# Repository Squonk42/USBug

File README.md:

USBug Development Board
=====

The USBug is a complete USB-based microcontroller development system in a very small footprint.
All programming is done via the USB port. No special programmer is needed, only a standard "Mini-B" USB cable and a Windows/Linux PC or a Macintosh with a USB port are required.

Key features:
 - Fully Open-Source Hardware & Software (CC-BY-SA, GPL)
 - Drag & Drop firmware, just use it as an USB Memory Stick!
 - No Loader application, the bootloader resides in ROM (unereasable)
 - Works with Mac OS X, Linux & Windows
 - Standard ARM SWD debug/trace connector
 - ARM "Cortex M3" 32-bit processor, up to 72 MHz, up to 64 kB Flash, up to 10 kB SRAM
 - Up to 42 GPIO pins, 1xUSB device, 1xUART, 1xI2C, 1xSPI interfaces
 - 2x32-bit, 2x16-bit, 1xWatchdog timers
 - 10 Bit ADC with up to 8 inputs
 - Tiny size: 2" x 0.8" (50 mm x 20 mm), only 0.244" (6.2 mm) thick (w/o header pins)
 - Available with pins for solderless breadboard
 - Very low cost & low shipping options

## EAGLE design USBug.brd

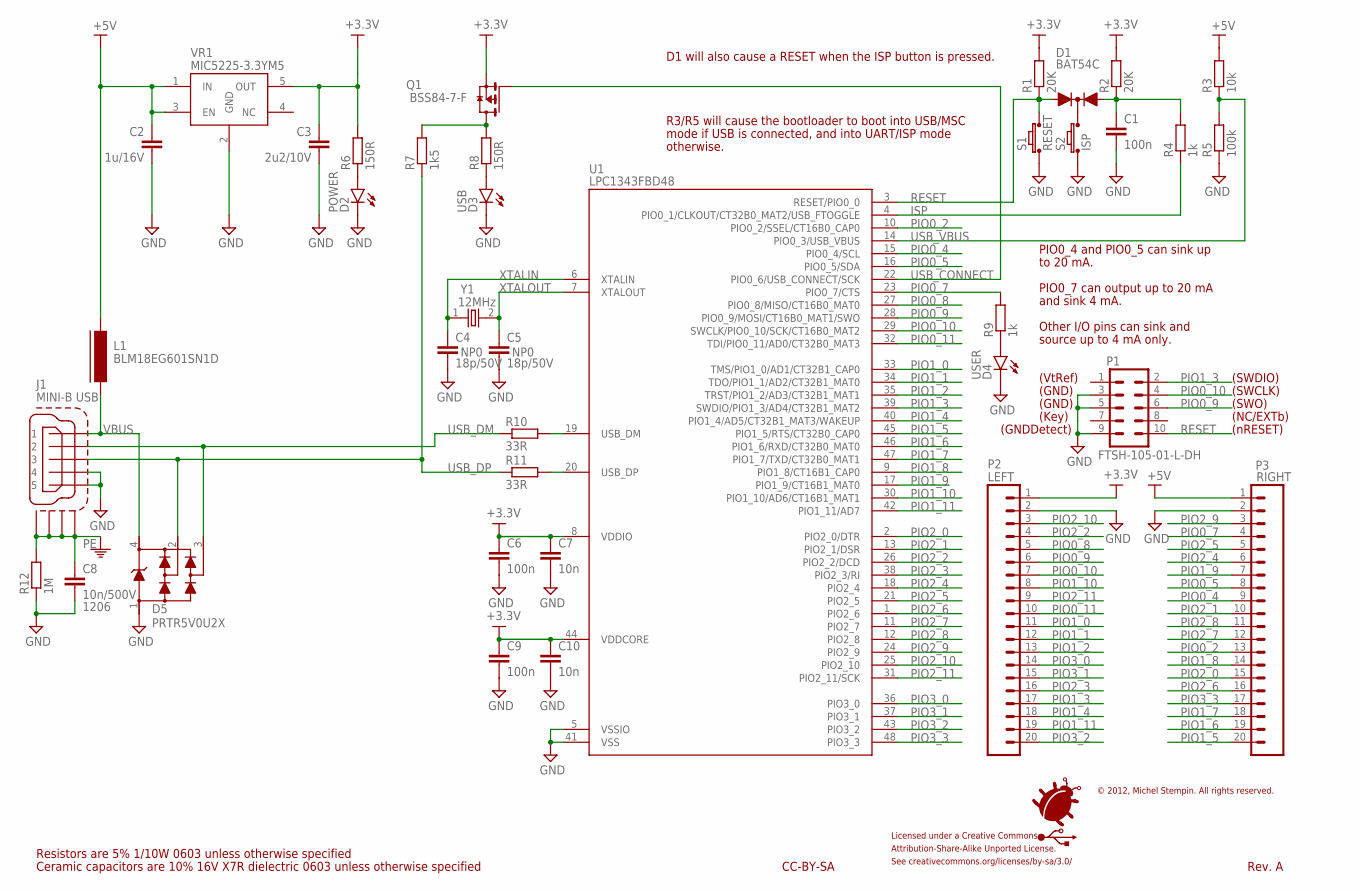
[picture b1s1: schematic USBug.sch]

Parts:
C1, C6, C9: 100n; CAP_0603
C2: 1u/16V; CAP_0603
C3: 2u2/10V; CAP_0603
C4, C5: 18p/50V; CAP_0603
C7, C10: 10n; CAP_0603
C8: 10n/500V; CAP_1206
D1: BAT54C; SOT23-R
D2: POWER; LED_0805
D3: USB; LED_0805
D4: USER; LED_0805
D5: PRTR5V0U2X; SOT143B
J1: MINI-B USB; UX60-MB-5ST
L1: BLM18EG601SN1D; FB_0603
LOGO: USBUG
P1: FTSH-105-01-L-DH
P2: LEFT; SPARKFUN_1X20_LOCK
P3: RIGHT; SPARKFUN_1X20_LOCK
Q1: BSS84-7-F; SOT23-R
R1, R2: 20K; RES_0603
R3: 10k; RES_0603
R4, R9: 1k; RES_0603
R5: 100k; RES_0603
R6, R8: 150R; RES_0603
R7: 1k5; RES_0603
R10, R11: 33R; RES_0603
R12: 1M; RES_0603
S1: RESET; ADTSM3
S2: ISP; ADTSM3
U1: LPC1343FBD48; LQFP48
VR1: MIC5225-3.3YM5; SOT23-5
Y1: 12MHz; NX5032GA

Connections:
+3.3V: C3.1, C6.1, C7.1, C9.1, C10.1, P2.1, Q1.2 (S), R1.2, R2.2, R6.2, U1.8 (VDDIO), U1.44 (VDDCORE), VR1.5 (OUT)
+5V: C2.1, L1.1, P3.1, R3.2, VR1.1 (IN), VR1.3 (EN)
GND: C1.2, C2.2, C3.2, C4.2, C5.2, C6.2, C7.2, C8.2, C9.2, C10.2, D2.C, D3.C, D4.C, D5.1, J1.4, J1.5, P1.3, P1.5, P1.9, P2.2, P3.2, R5.1, R12.1, S1.2, S2.2, U1.5 (VSSIO), U1.41 (VSS), VR1.2 (GND)
ISP: R4.1, U1.4 (PIO0_1/CLKOUT/CT32B0_MAT2/USB_FTOGGLE)
unnamed: D1.3 (C), S2.1
unnamed: C1.1, D1.2 (A2), R2.1, R4.2
unnamed: D2.A, R6.1
unnamed: D4.A, R9.1
unnamed: D3.A, R8.1
unnamed: Q1.3 (D), R7.2, R8.2
PE: C8.1, J1.M1, J1.M2, J1.M3, J1.M4, R12.2
PIO0_2: P3.13, U1.10 (PIO0_2/SSEL/CT16B0_CAP0)
PIO0_4: P3.9, U1.15 (PIO0_4/SCL)
PIO0_5: P3.8, U1.16 (PIO0_5/SDA)
PIO0_7: P3.4, R9.2, U1.23 (PIO0_7/CTS)
PIO0_8: P2.5, U1.27 (PIO0_8/MISO/CT16B0_MAT0)
PIO0_9: P1.6, P2.6, U1.28 (PIO0_9/MOSI/CT16B0_MAT1/SWO)
PIO0_10: P1.4, P2.7, U1.29 (SWCLK/PIO0_10/SCK/CT16B0_MAT2)
PIO0_11: P2.10, U1.32 (TDI/PIO0_11/AD0/CT32B0_MAT3)
PIO1_0: P2.11, U1.33 (TMS/PIO1_0/AD1/CT32B1_CAP0)
PIO1_1: P2.12, U1.34 (TDO/PIO1_1/AD2/CT32B1_MAT0)
PIO1_2: P2.13, U1.35 (TRST/PIO1_2/AD3/CT32B1_MAT1)
PIO1_3: P1.2, P2.17, U1.39 (SWDIO/PIO1_3/AD4/CT32B1_MAT2)
PIO1_4: P2.18, U1.40 (PIO1_4/AD5/CT32B1_MAT3/WAKEUP)
PIO1_5: P3.20, U1.45 (PIO1_5/RTS/CT32B0_CAP0)
PIO1_6: P3.19, U1.46 (PIO1_6/RXD/CT32B0_MAT0)
PIO1_7: P3.18, U1.47 (PIO1_7/TXD/CT32B0_MAT1)
PIO1_8: P3.14, U1.9 (PIO1_8/CT16B1_CAP0)
PIO1_9: P3.7, U1.17 (PIO1_9/CT16B1_MAT0)
PIO1_10: P2.8, U1.30 (PIO1_10/AD6/CT16B1_MAT1)
PIO1_11: P2.19, U1.42 (PIO1_11/AD7)
PIO2_0: P3.15, U1.2 (PIO2_0/DTR)
PIO2_1: P3.10, U1.13 (PIO2_1/DSR)
PIO2_2: P2.4, U1.26 (PIO2_2/DCD)
PIO2_3: P2.16, U1.38 (PIO2_3/RI)
PIO2_4: P3.6, U1.18 (PIO2_4)
PIO2_5: P3.5, U1.21 (PIO2_5)
PIO2_6: P3.16, U1.1 (PIO2_6)
PIO2_7: P3.12, U1.11 (PIO2_7)
PIO2_8: P3.11, U1.12 (PIO2_8)
PIO2_9: P3.3, U1.24 (PIO2_9)
PIO2_10: P2.3, U1.25 (PIO2_10)
PIO2_11: P2.9, U1.31 (PIO2_11/SCK)
PIO3_0: P2.14, U1.36 (PIO3_0)
PIO3_1: P2.15, U1.37 (PIO3_1)
PIO3_2: P2.20, U1.43 (PIO3_2)
PIO3_3: P3.17, U1.48 (PIO3_3)
RESET: D1.1 (A1), P1.10, R1.1, S1.1, U1.3 (RESET/PIO0_0)
USBD+: R10.2, U1.19 (USB_DM)
USBD-: R11.2, U1.20 (USB_DP)
USB_CONNECT: Q1.1 (G), U1.22 (PIO0_6/USB_CONNECT/SCK)
USB_DM: D5.3, J1.2, R10.1
USB_DP: D5.2, J1.3, R7.1, R11.1
USB_VBUS: R3.1, R5.2, U1.14 (PIO0_3/USB_VBUS)
VBUS: D5.4, J1.1, L1.2
XTALIN: C4.1, U1.6 (XTALIN), Y1.1
XTALOUT: C5.1, U1.7 (XTALOUT), Y1.2

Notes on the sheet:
Rev. A
PIO0_7 can output up to 20 mA
and sink 4 mA.
PIO0_4 and PIO0_5 can sink up
to 20 mA.
Other I/O pins can sink and
source up to 4 mA only.
D1 will also cause a RESET when the ISP button is pressed.
R3/R5 will cause the bootloader to boot into USB/MSC
mode if USB is connected, and into UART/ISP mode
otherwise.
© 2012, Michel Stempin. All rights reserved.
Licensed under a Creative Commons
Attribution-Share-Alike Unported License.
See creativecommons.org/licenses/by-sa/3.0/
(SWDIO)
(SWCLK)
(SWO)
(VtRef)
(GND)
(Key)
(NC/EXTb)
(GNDDetect)
(nRESET)
Ceramic capacitors are 10% 16V X7R dielectric 0603 unless otherwise specified
Resistors are 5% 1/10W 0603 unless otherwise specified
CC-BY-SA

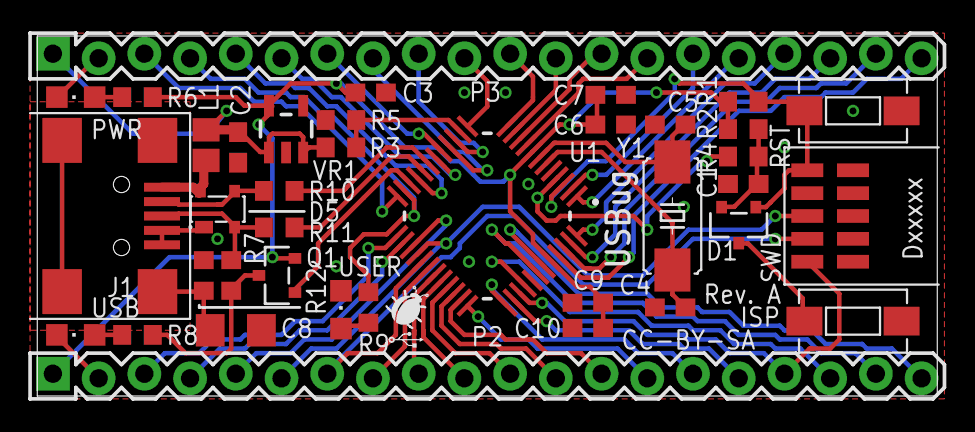
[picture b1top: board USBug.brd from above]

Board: 2 copper layers, 50.0 x 20.0 mm, 39 parts (0 on the bottom side), 57 nets.

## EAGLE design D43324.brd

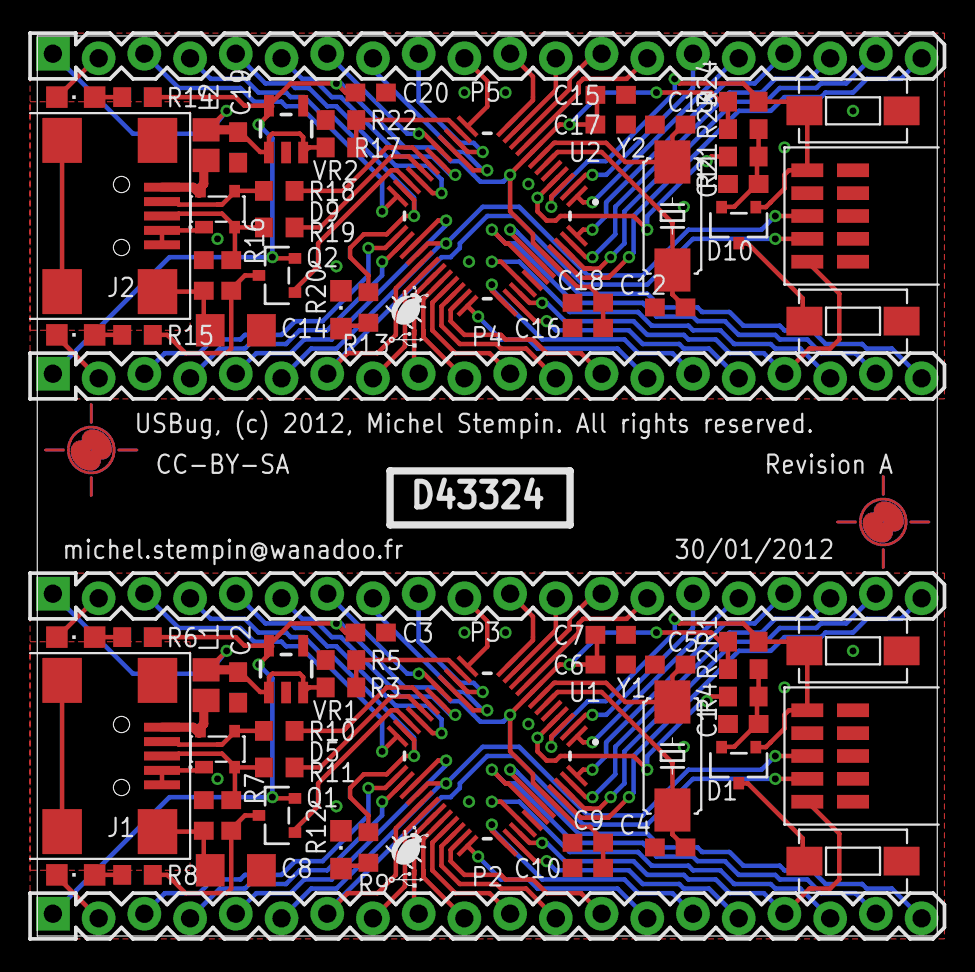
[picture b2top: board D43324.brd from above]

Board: 2 copper layers, 50.0 x 50.0 mm, 80 parts (0 on the bottom side), 114 nets.

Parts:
C1, C6, C9, C11, C17, C18: 100n; CAP_0603
C2, C19: 1u/16V; CAP_0603
C3, C20: 2u2/10V; CAP_0603
C4, C5, C12, C13: 18p/50V; CAP_0603
C7, C10, C15, C16: 10n; CAP_0603
C8, C14: 10n/500V; CAP_1206
D1, D10: BAT54C; SOT23-R
D2, D7: POWER; LED_0805
D3, D8: USB; LED_0805
D4, D6: USER; LED_0805
D5, D9: PRTR5V0U2X; SOT143B
E$1, E$2: PASS-ROUND
E$3: USBUG
J1, J2: MINI-B USB; UX60-MB-5ST
L1, L2: BLM18EG601SN1D; FB_0603
P1, P6: FTSH-105-01-L-DH
P2, P4: LEFT; SPARKFUN_1X20_LOCK
P3, P5: RIGHT; SPARKFUN_1X20_LOCK
Q1, Q2: BSS84-7-F; SOT23-R
R1, R2, R23, R24: 20K; RES_0603
R3, R17: 10k; RES_0603
R4, R9, R13, R21: 1k; RES_0603
R5, R22: 100k; RES_0603
R6, R8, R14, R15: 150R; RES_0603
R7, R16: 1k5; RES_0603
R10, R11, R18, R19: 33R; RES_0603
R12, R20: 1M; RES_0603
S1, S4: RESET; ADTSM3
S2, S3: ISP; ADTSM3
U1, U2: LPC11U12FBD48; LQFP48
U$13: USBUG
VR1, VR2: MIC5225-3.3YM5; SOT23-5
Y1, Y2: 12MHz; NX5032GA

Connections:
+3.3V: C3.1, C6.1, C7.1, C9.1, C10.1, P2.1, Q1.2, R1.2, R2.2, R6.2, U1.8, U1.44, VR1.5
+3.3V1: C15.1, C16.1, C17.1, C18.1, C20.1, P4.1, Q2.2, R14.2, R23.2, R24.2, U2.8, U2.44, VR2.5
+5V: C2.1, L1.1, P3.1, R3.2, VR1.1, VR1.3
+5V1: C19.1, L2.1, P5.1, R17.2, VR2.1, VR2.3
EARTH: C8.1, J1.M1, J1.M2, J1.M3, J1.M4, R12.2
EARTH1: C14.1, J2.M1, J2.M2, J2.M3, J2.M4, R20.2
GND: C1.2, C2.2, C3.2, C4.2, C5.2, C6.2, C7.2, C8.2, C9.2, C10.2, D2.C, D3.C, D4.C, D5.1, J1.4, J1.5, P1.3, P1.5, P1.9, P2.2, P3.2, R5.1, R12.1, S1.2, S2.2, U1.5, U1.41, VR1.2
GND1: C11.2, C12.2, C13.2, C14.2, C15.2, C16.2, C17.2, C18.2, C19.2, C20.2, D6.C, D7.C, D8.C, D9.1, J2.4, J2.5, P4.2, P5.2, P6.3, P6.5, P6.9, R20.1, R22.1, S3.2, S4.2, U2.5, U2.41, VR2.2
ISP: R4.1, U1.4
ISP1: R21.1, U2.4
unnamed: D1.3, S2.1
unnamed: C1.1, D1.2, R2.1, R4.2
unnamed: D2.A, R6.1
unnamed: D4.A, R9.1
unnamed: Q2.3, R15.2, R16.2
unnamed: C11.1, D10.2, R21.2, R23.1
unnamed: D7.A, R14.1
unnamed: D6.A, R13.1
unnamed: D3.A, R8.1
unnamed: D8.A, R15.1
unnamed: D10.3, S3.1
unnamed: Q1.3, R7.2, R8.2
PIO0_1: P4.5, U2.27
PIO0_2: P3.13, U1.10
PIO0_3: P4.6, P6.6, U2.28
PIO0_4: P3.9, U1.15
PIO0_5: P3.8, U1.16
PIO0_6: P4.7, P6.4, U2.29
PIO0_7: P3.4, R9.2, U1.23
PIO0_8: P2.5, U1.27
PIO0_9: P1.6, P2.6, U1.28
PIO0_10: P1.4, P2.7, U1.29
PIO0_11: P2.10, U1.32
PIO0_12: P4.10, U2.32
PIO0_13: P5.4, R13.2, U2.23
PIO0_14: P5.8, U2.16
PIO0_15: P5.9, U2.15
PIO0_16: P5.13, U2.10
PIO1_0: P2.11, U1.33
PIO1_1: P2.12, U1.34
PIO1_2: P2.13, U1.35
PIO1_3: P1.2, P2.17, U1.39
PIO1_4: P2.18, U1.40
PIO1_5: P3.20, U1.45
PIO1_6: P3.19, U1.46
PIO1_7: P3.18, U1.47
PIO1_8: P3.14, U1.9
PIO1_9: P3.7, U1.17
PIO1_10: P2.8, U1.30
PIO1_11: P2.19, U1.42
PIO1_12: P5.14, U2.9
PIO1_13: P5.7, U2.17
PIO1_14: P4.8, U2.30
PIO1_15: P4.19, U2.42
PIO1_16: P5.20, U2.45
PIO1_17: P4.11, U2.33
PIO1_18: P4.12, U2.34
PIO1_19: P4.13, U2.35
PIO1_20: P4.17, P6.2, U2.39
PIO1_21: P4.18, U2.40
PIO1_22: P5.18, U2.47
PIO1_23: P5.19, U2.46
PIO2_0: P3.15, U1.2
PIO2_1: P3.10, U1.13
PIO2_2: P2.4, U1.26
PIO2_3: P2.16, U1.38
PIO2_4: P3.6, U1.18
PIO2_5: P3.5, U1.21
PIO2_6: P3.16, U1.1
PIO2_7: P3.12, U1.11
PIO2_8: P3.11, U1.12
PIO2_9: P3.3, U1.24
PIO2_10: P2.3, U1.25
PIO2_11: P2.9, U1.31
PIO2_12: P5.10, U2.13
PIO2_13: P4.4, U2.26
PIO2_14: P4.16, U2.38
PIO2_15: P5.6, U2.18
PIO2_16: P5.5, U2.21
PIO2_17: P5.16, U2.1
PIO2_18: P5.12, U2.11
PIO2_19: P5.11, U2.12
PIO2_20: P5.3, U2.24
PIO2_21: P4.3, U2.25
PIO2_22: P4.9, U2.31
PIO2_23: P5.15, U2.2
PIO3_0: P2.14, U1.36
PIO3_1: P2.15, U1.37
PIO3_2: P2.20, U1.43
PIO3_3: P3.17, U1.48
PIO3_4: P4.14, U2.36
PIO3_5: P4.15, U2.37
PIO3_6: P4.20, U2.43
PIO3_7: P5.17, U2.48
RESET: D1.1, P1.10, R1.1, S1.1, U1.3
RESET1: D10.1, P6.10, R24.1, S4.1, U2.3
USBD+: R10.2, U1.19
USBD+1: R18.2, U2.19
USBD-: R11.2, U1.20
USBD-1: R19.2, U2.20
USB_CONNECT: Q1.1, U1.22
USB_CONNECT1: Q2.1, U2.22
USB_DM: D5.3, J1.2, R10.1
USB_DM1: D9.3, J2.2, R18.1
USB_DP: D5.2, J1.3, R7.1, R11.1
USB_DP1: D9.2, J2.3, R16.1, R19.1
USB_VBUS: R3.1, R5.2, U1.14
USB_VBUS1: R17.1, R22.2, U2.14
VBUS: D5.4, J1.1, L1.2
VBUS1: D9.4, J2.1, L2.2
XTALIN: C4.1, U1.6, Y1.1
XTALIN1: C12.1, U2.6, Y2.1
XTALOUT: C5.1, U1.7, Y1.2
XTALOUT1: C13.1, U2.7, Y2.2

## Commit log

2012-05-15 First public release
2012-05-15 Removed empty README file
2012-06-03 Deleted old USBUg DigiKey BOM. Added both Digikey and Farnell baskets.
2012-06-23 Create gh-pages branch via GitHub
2012-06-23 Added Progression800.png
2012-06-23 Update gh-pages
2012-06-23 Added USBug_Logo.png
2012-06-24 Lots of changes to get a first working page!
2012-06-24 Small change to remove OEM mention
2012-06-24 More improvements
2012-06-24 Added CPU comparison table
2012-06-25 Removed too commercial sections
2012-06-25 Added blog on CPU variant
2012-06-25 Added some blob on the CPU variants
2012-06-25 Typos
2012-06-25 More typos!
2012-06-25 Added missing labels
2012-06-26 Added component datasheet links
2012-06-28 Added a DataTables JQuery plug-in for the CPU variant table
2012-06-28 Fixed wrong information in Key Features
2012-06-29 typo
2012-06-29 Minor changes
2012-06-29 Added non-sortable CPU columns
2012-07-01 Added SeaDragon Deep Zoom Schematic view
2012-07-01 Added High-resolution layout bitmap
2012-07-01 Added images directory
2012-07-01 Added picture dispay using FancyBox overlay
2012-07-01 Added BOM DataTable
2012-07-01 Added YouTube videos
2012-07-09 Added Google Analytics + menu test
2012-07-09 Added legal terms.
2012-07-09 Link errors
2012-07-09 Closed Open tags
2012-07-09 Added favicon.ico
2012-07-09 Forced favicon in header
2012-07-10 Added Board-Comparison.jpg
2012-07-15 Added 3D panorama
2012-07-15 Added LittleWire panorama
2012-07-19 Added test files
2012-10-04 Removed img box-shadow
2012-12-02 Added Disqus comments

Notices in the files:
D43324.brd:
USBug, (c) 2012, Michel Stempin. All rights reserved.
parts and their libraries:
USBug: Derived from work by Mushii (Own work) [CC-BY-SA-3.0 (www.creativecommons.org/licenses/by-sa/3.0) or GFDL (www.gnu.org/copyleft/fdl.html)], via Wikimedia Commons
